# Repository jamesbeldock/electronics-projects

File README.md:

# Electronics Projects

Various electronics projects, mostly for home automation. I am not a professional electrical engineer. See Disclaimer :) 

## LED Control Board `XC-0001 Rev 2`

Originally designed to power 12V lighted house numerals from Luxello and constant-current LEDs using an off-board part.

## Disclaimer
This repository contains electronics designs, schematics, board layouts, firmware, and related materials (the "Materials") provided for educational and informational purposes only. The Materials are distributed under the MIT License (see LICENSE).

**No warranty.** The Materials are provided "AS IS", without warranty of any kind, express or implied, including but not limited to the warranties of merchantability, fitness for a particular purpose, correctness, and non-infringement. No representation is made that any design is safe, functional, complete, accurate, or suitable for any purpose.
Assumption of risk. Working with electronics involves inherent risks, including but not limited to electric shock, fire, burns, exposure to hazardous materials, damage to property, and bodily injury or death — particularly where mains voltage, lithium chemistries, high currents, RF emissions, or stored energy (capacitors, inductors) are involved. You assume all risk arising from any use, construction, modification, or operation of the Materials.

**No liability.** In no event shall the author(s) or copyright holder(s) be liable for any claim, damages, or other liability — whether in an action of contract, tort (including negligence), or otherwise — arising from, out of, or in connection with the Materials or their use, including any direct, indirect, incidental, special, exemplary, consequential, or punitive damages, regardless of the theory of liability and even if advised of the possibility of such damages.

**Your responsibility.** You are solely responsible for verifying every design before use; for ensuring compliance with all applicable codes, standards, and regulations (including but not limited to electrical, building, fire, and RF/EMC regulations such as those of the FCC, IEC, UL, and CE); for obtaining any required certifications or inspections; and for the safe construction, testing, and operation of anything derived from the Materials. Designs are not certified, have not necessarily been tested, and may contain errors, omissions, or latent defects.

**Not professional advice.** Nothing herein constitutes engineering, legal, or safety advice. Consult a qualified licensed professional before relying on any design.

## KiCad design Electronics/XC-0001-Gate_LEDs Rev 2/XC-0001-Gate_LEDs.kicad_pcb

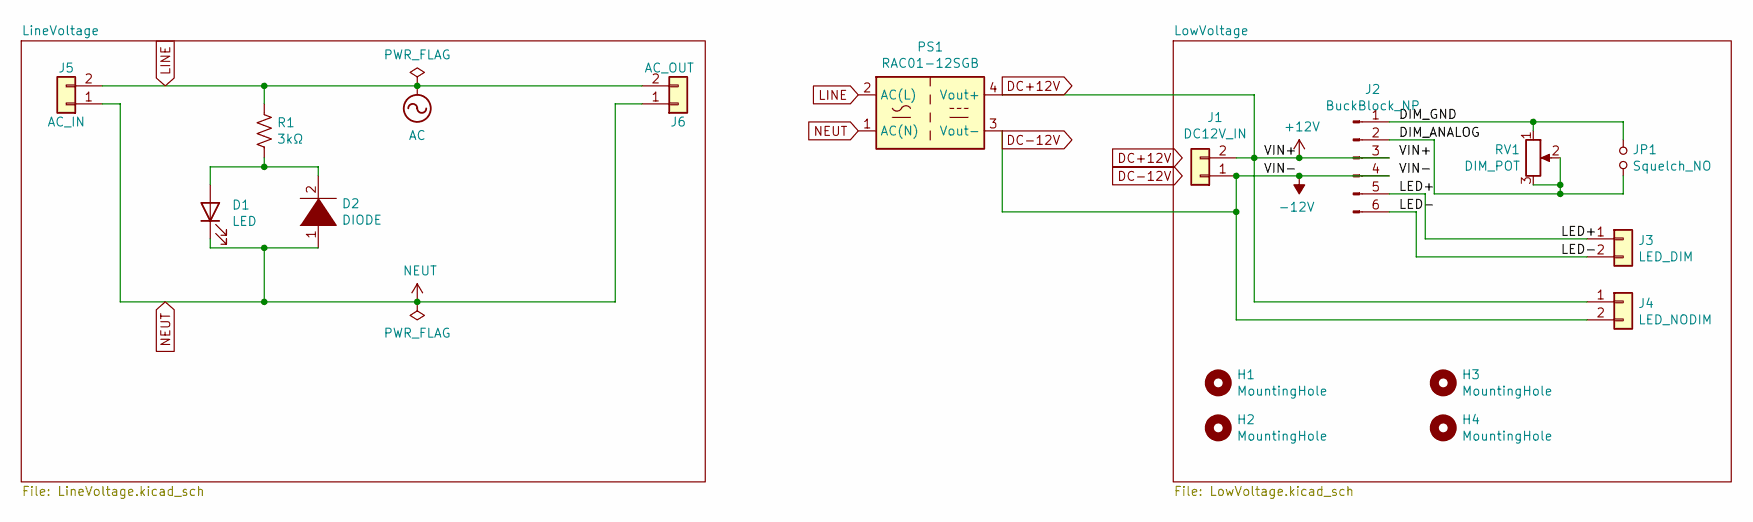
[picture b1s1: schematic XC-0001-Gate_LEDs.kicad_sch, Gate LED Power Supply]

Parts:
D1: LED; SolderWire-0.5sqmm_1x02_P4.8mm_D0.9mm_OD2.3mm
D2: DIODE; D_T-1_P10.16mm_Horizontal
H1, H2, H3, H4: MountingHole; MountingHole_3.2mm_M3_DIN965_Pad_TopOnly
J1: DC12V_IN; SolderWire-0.25sqmm_1x02_P4.2mm_D0.65mm_OD1.7mm
J2: BuckBlock_NP; SolderWire-1sqmm_1x06_P7.8mm_D1.4mm_OD3.9mm
J3: LED_DIM; SolderWire-0.25sqmm_1x02_P4.2mm_D0.65mm_OD1.7mm
J4: LED_NODIM; SolderWire-0.25sqmm_1x02_P4.2mm_D0.65mm_OD1.7mm
J5: AC_IN; SolderWire-0.75sqmm_1x02_P7mm_D1.25mm_OD3.5mm
J6: AC_OUT; SolderWire-0.75sqmm_1x02_P7mm_D1.25mm_OD3.5mm
JP1: Squelch_NO; SolderWire-0.25sqmm_1x02_P4.2mm_D0.65mm_OD1.7mm
PS1: RAC01-12SGB; Converter_ACDC_RECOM_RAC01-xxSGB_THT
R1: 3kΩ; R_1210_3225Metric_Pad1.30x2.65mm_HandSolder
RV1: DIM_POT; Potentiometer_Piher_PC-16_Single_Horizontal

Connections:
+12V: J1.2, J2.3, J4.1, PS1.4 (Vout+)
/DIM_ANALOG: J2.2, JP1.2, RV1.2, RV1.3
/DIM_GND: J2.1, JP1.1, RV1.1
/LED+: J2.5, J3.1
/LED-: J2.6, J3.2
DC-12V: J1.1, J2.4, J4.2, PS1.3 (Vout-)
LINE: J5.2, J6.2, PS1.2 (AC(L)), R1.1
NEUT: D1.1 (K), D2.1 (K), J5.1, J6.1, PS1.1 (AC(N))
unnamed: D1.2 (A), D2.2 (A), R1.2

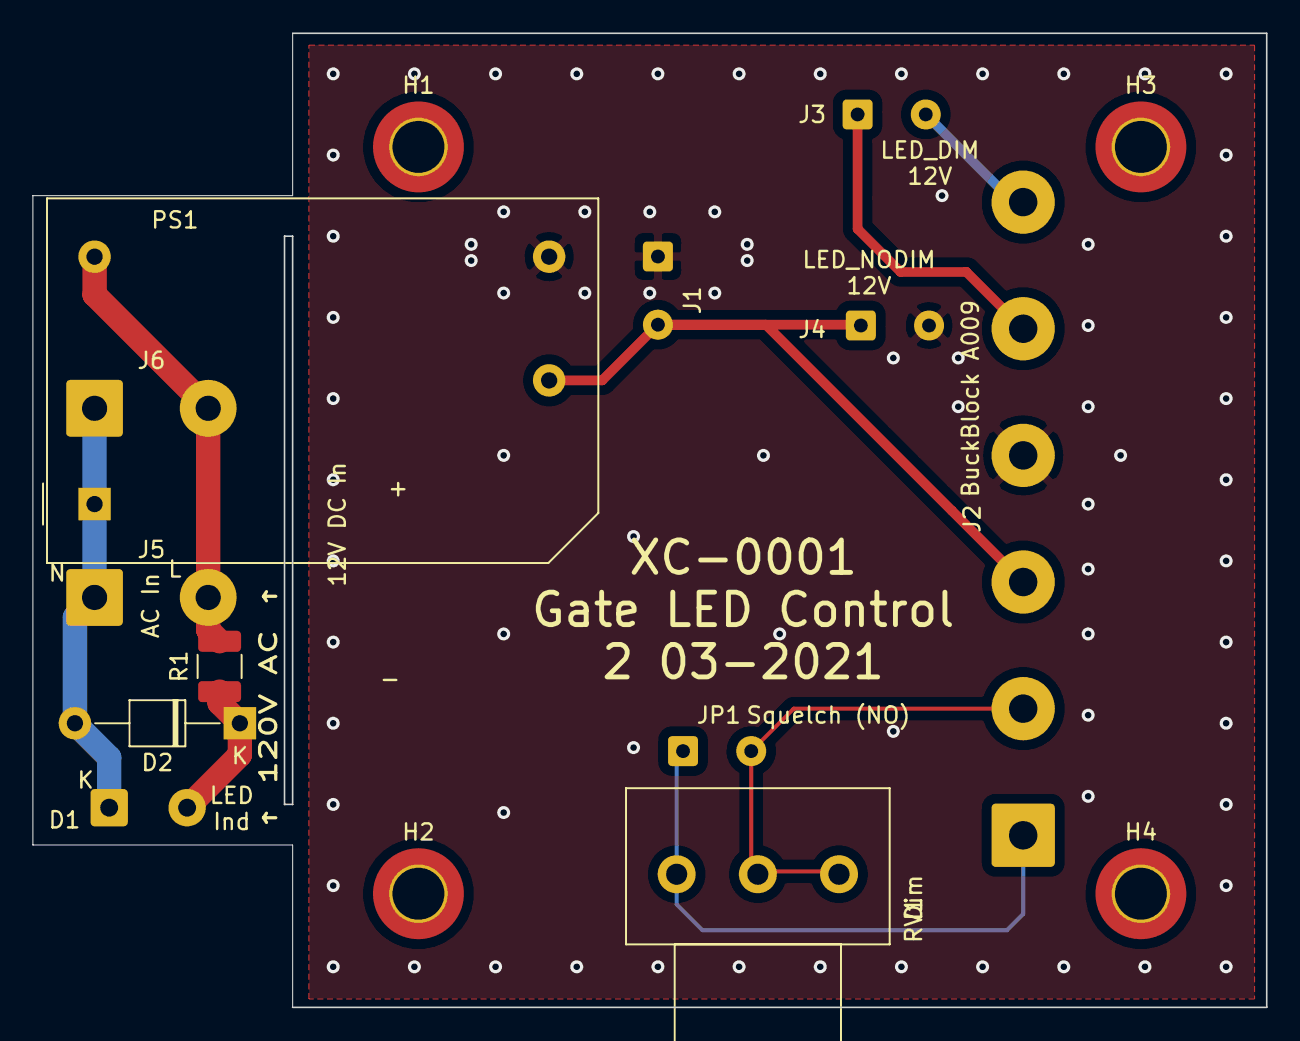
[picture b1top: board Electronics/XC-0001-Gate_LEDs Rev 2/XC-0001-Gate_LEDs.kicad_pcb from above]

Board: 2 copper layers, 76.0 x 60.0 mm, 16 parts (0 on the bottom side), 9 nets.

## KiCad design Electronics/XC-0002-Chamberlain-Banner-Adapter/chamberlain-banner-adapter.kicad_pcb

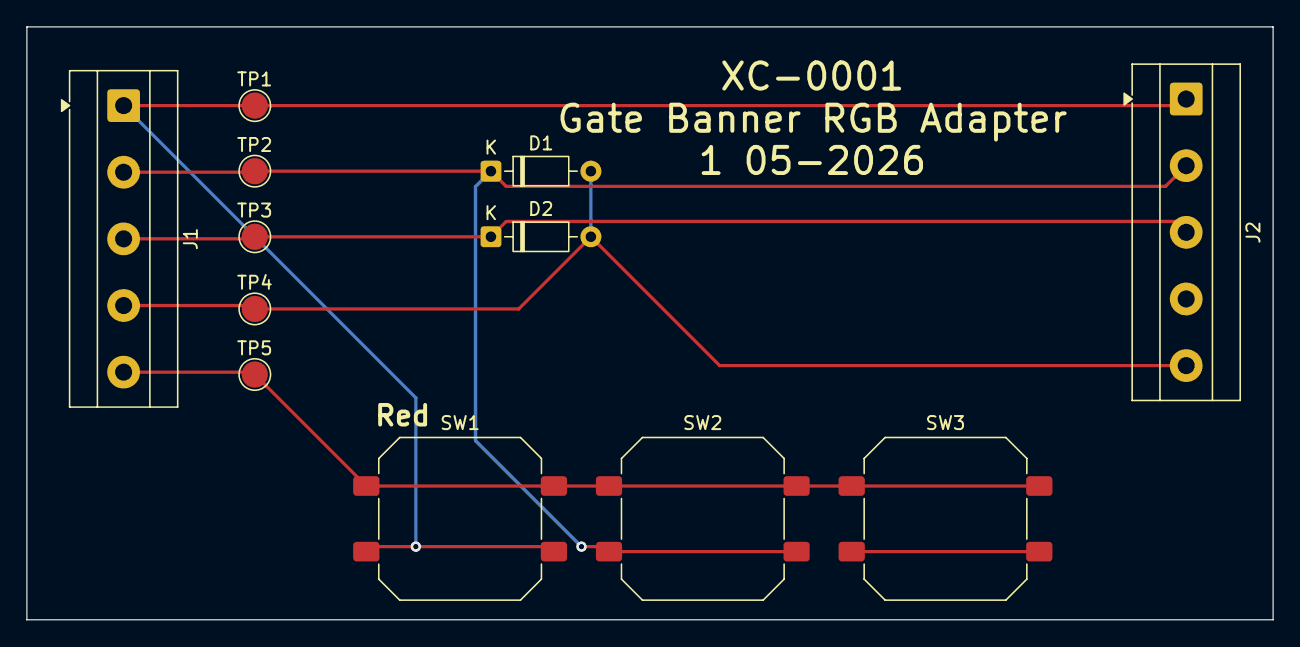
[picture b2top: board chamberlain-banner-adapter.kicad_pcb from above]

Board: 2 copper layers, 95.0 x 45.2 mm, 12 parts (0 on the bottom side), 5 nets.

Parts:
D1, D2: 1N914; D_DO-35_SOD27_P7.62mm_Horizontal
J1, J2: Conn_01x05_Socket; TerminalBlock_MetzConnect_Type101_RT01605HBWC_1x05_P5.08mm_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
SW1, SW2, SW3: SW_Push; SW_Push_1P1T_NO_CK_PTS125Sx43SMTR
TP1, TP2, TP3, TP4, TP5: TestPoint; TestPoint_Pad_D2.0mm

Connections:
/Blink: D1.2 (A), D2.2 (A), J1.4, J2.5, TP4.1 (1_1)
/Com –: J1.1, J2.1, SW1.2, TP1.1 (1_1)
/Green Output: D2.1 (K), J1.3, J2.3, TP3.1 (1_1)
/Red Output: D1.1 (K), J1.2, J2.2, SW2.2, TP2.1 (1_1)
unnamed: J1.5, SW1.1, SW2.1, SW3.1 (1_1), TP5.1 (1_1)

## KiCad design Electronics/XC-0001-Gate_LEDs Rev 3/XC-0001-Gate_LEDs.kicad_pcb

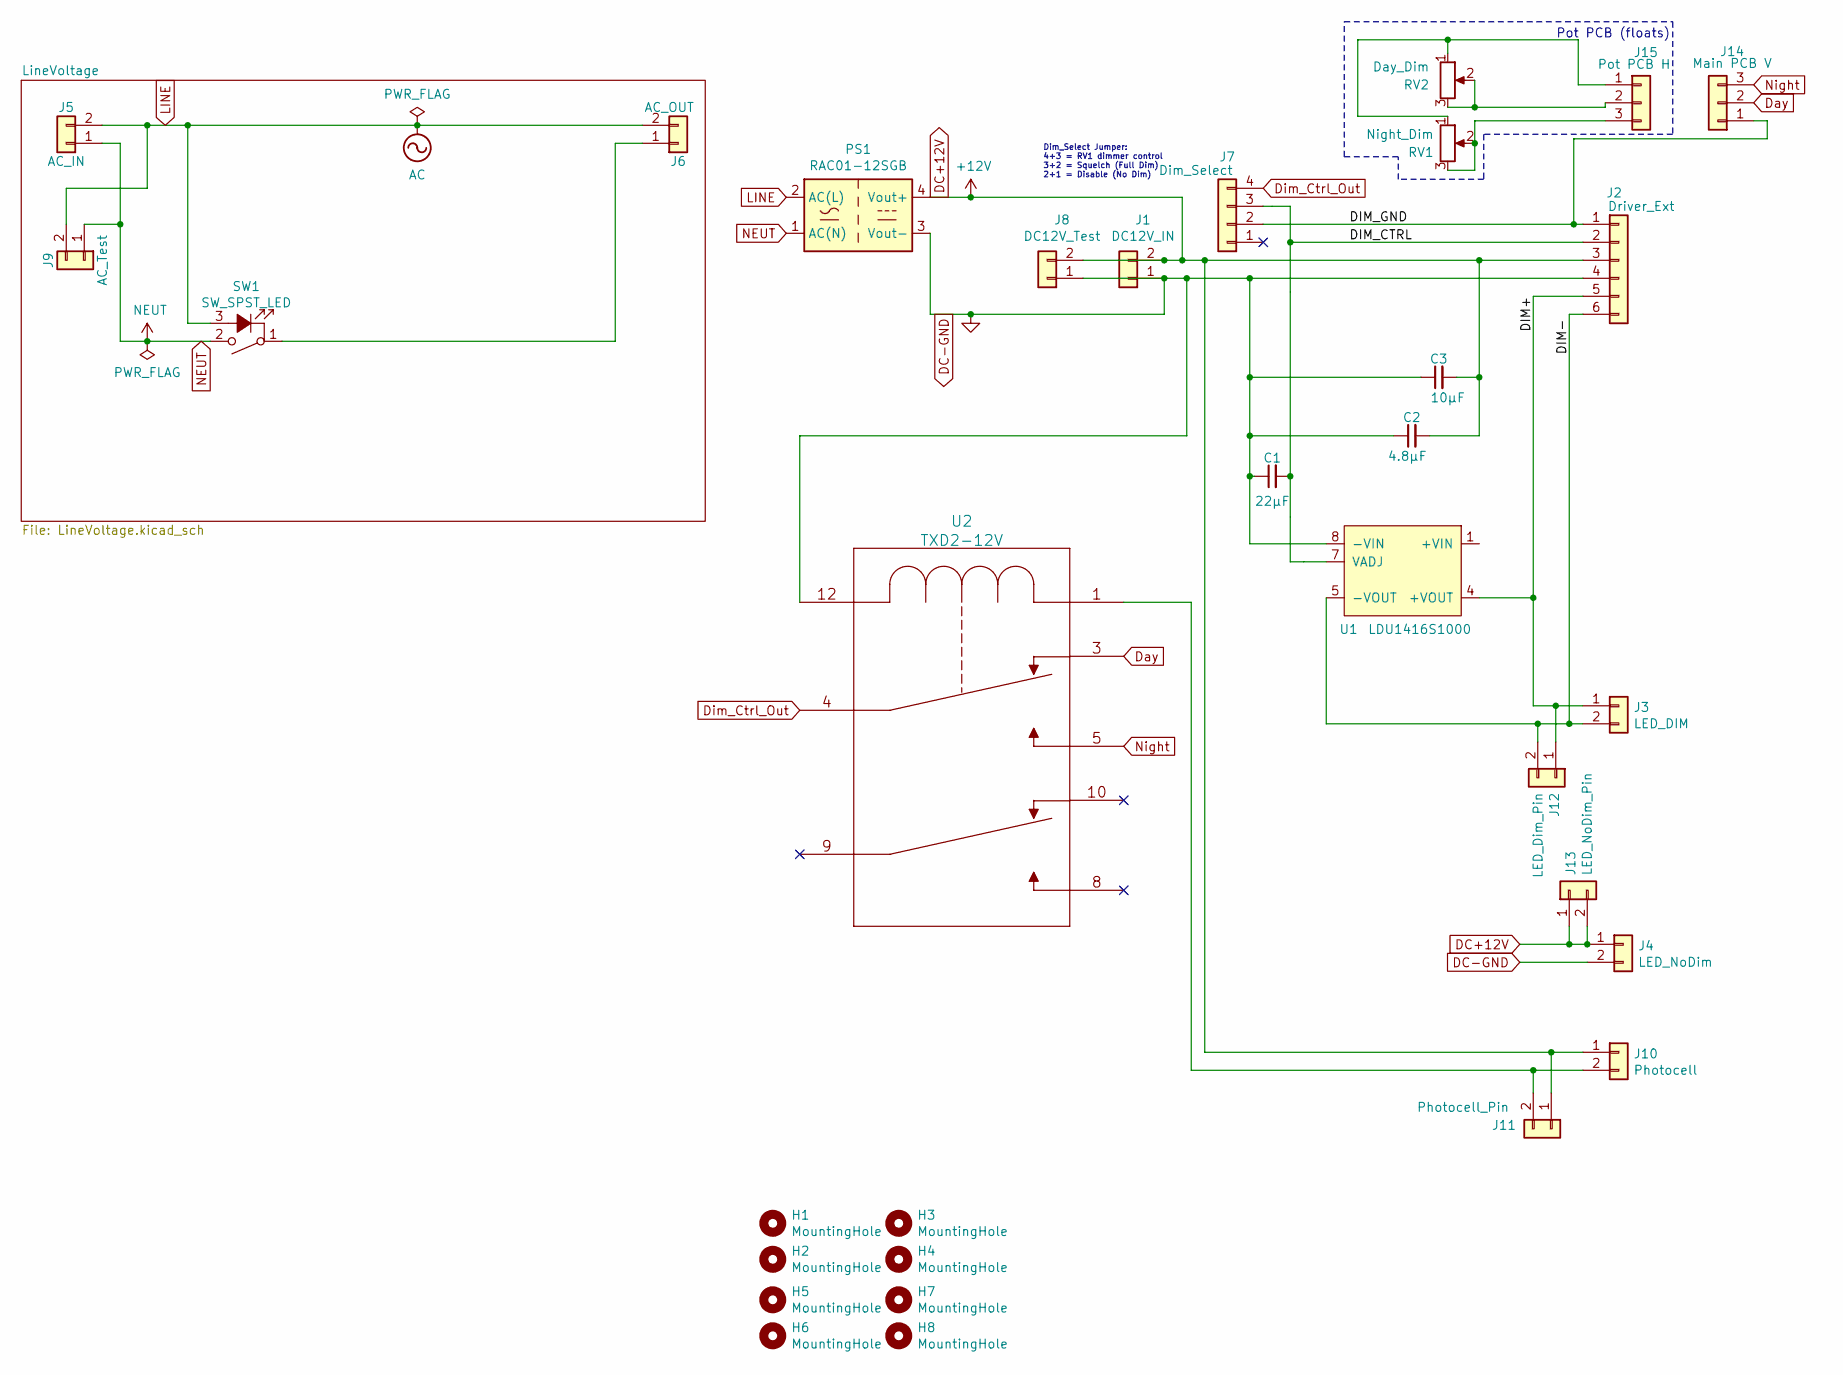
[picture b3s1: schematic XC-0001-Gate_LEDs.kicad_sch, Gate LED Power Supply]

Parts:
C1: 22µF; C_1206_3216Metric_Pad1.33x1.80mm_HandSolder; Digikey 1276-3107-1-ND
C2: 4.8µF; C_1206_3216Metric_Pad1.33x1.80mm_HandSolder; Digikey 1276-1133-1-ND
C3: 10µF; C_1206_3216Metric_Pad1.33x1.80mm_HandSolder; Digikey 1276-3147-1-ND
H1, H2, H3, H4, H5, H6, H7, H8: MountingHole; MountingHole_3.2mm_M3
J1: DC12V_IN; SolderWire-1.5sqmm_1x02_P7.8mm_D1.7mm_OD3.9mm
J2: Driver_Ext; SolderWire-1.5sqmm_1x06_Grouped2x3_P6mm_D1.7mm_OD3mm
J3: LED_DIM; PhoenixContact_MSTBA_2,5_2-G-5,08_1x02_P5.08mm_Horizontal
J4: LED_NoDim; PhoenixContact_MSTBA_2,5_2-G-5,08_1x02_P5.08mm_Horizontal
J5: AC_IN; 6160.0015 C8 Inlet (panel mount, PCB pins)
J6: AC_OUT; SolderWire-2sqmm_1x02_P7.8mm_D2mm_OD3.9mm_Relief
J7: Dim_Select; PinHeader_1x04_P2.54mm_Vertical; Digikey MTSW-104-07-G-S-170-ND
J8: DC12V_Test; Test Holes
J9: AC_Test; Test Holes
J10: Photocell; PhoenixContact_MSTBA_2,5_2-G-5,08_1x02_P5.08mm_Horizontal
J11: Photocell_Pin; PinHeader_1x02_P2.54mm_Vertical
J12: LED_Dim_Pin; PinHeader_1x02_P2.54mm_Vertical
J13: LED_NoDim_Pin; PinHeader_1x02_P2.54mm_Vertical
J14: Main PCB V; PinHeader_1x03_P2.54mm_Vertical
J15: Pot PCB H; PinHeader_1x03_P2.54mm_Vertical
PS1: RAC01-12SGB; Converter_ACDC_RECOM_RAC01-xxSGB_THT; Digikey ‎945-3046-ND‎
RV1: Night_Dim; Potentiometer_Piher_PC-16_Single_Horizontal; Digikey PDB181-K420K-203B-ND
RV2: Day_Dim; Potentiometer_Piher_PC-16_Single_Horizontal; Digikey PDB181-K420K-203B-ND
SW1: SW_SPST_LED; PhoenixContact_MSTBVA_2,5_3-G-5,08_1x03_P5.08mm_Vertical
U1: LDU1416S1000; Digikey ‎1470-2154-5-ND‎
U2: TXD2-12V; Digikey 255-2320-5-ND

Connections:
/DIM+: J2.5, J3.1, J12.1, U1.4 (+VOUT)
/DIM-: J2.6, J3.2, J12.2, U1.5 (-VOUT)
/DIM_CTRL: C1.2, J2.2, J7.3, U1.7 (VADJ)
/DIM_GND: J2.1, J7.2, J14.1
DC+12V: C2.2, C3.2, J1.2, J2.3, J4.1, J8.2, J10.1, J11.1, J13.1, J13.2, PS1.4 (Vout+); also elsewhere on the board
DC-GND: C1.1, C2.1, C3.1, J1.1, J2.4, J4.2, J8.1, PS1.3 (Vout-), U1.8 (-VIN), U2.12
Day: J14.2, U2.3
Dim_Ctrl_Out: J7.4, U2.4
LINE: J5.2, J6.2, J9.2, PS1.2 (AC(L)), SW1.3 (Line_In)
NEUT: J5.1, J9.1, PS1.1 (AC(N)), SW1.2 (Neutral_In)
unnamed: J6.1, SW1.1 (Neutral_Out)
unnamed: J10.2, J11.2, U2.1
unnamed: J15.1, RV1.1, RV2.1
unnamed: J15.3, RV1.2, RV1.3
unnamed: J15.2, RV2.2, RV2.3
Night: J14.3, U2.5

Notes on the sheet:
Dim_Select Jumper: 4+3 = RV1 dimmer control 3+2 = Squelch (Full Dim) 2+1 = Disable (No Dim)
Pot PCB (floats)

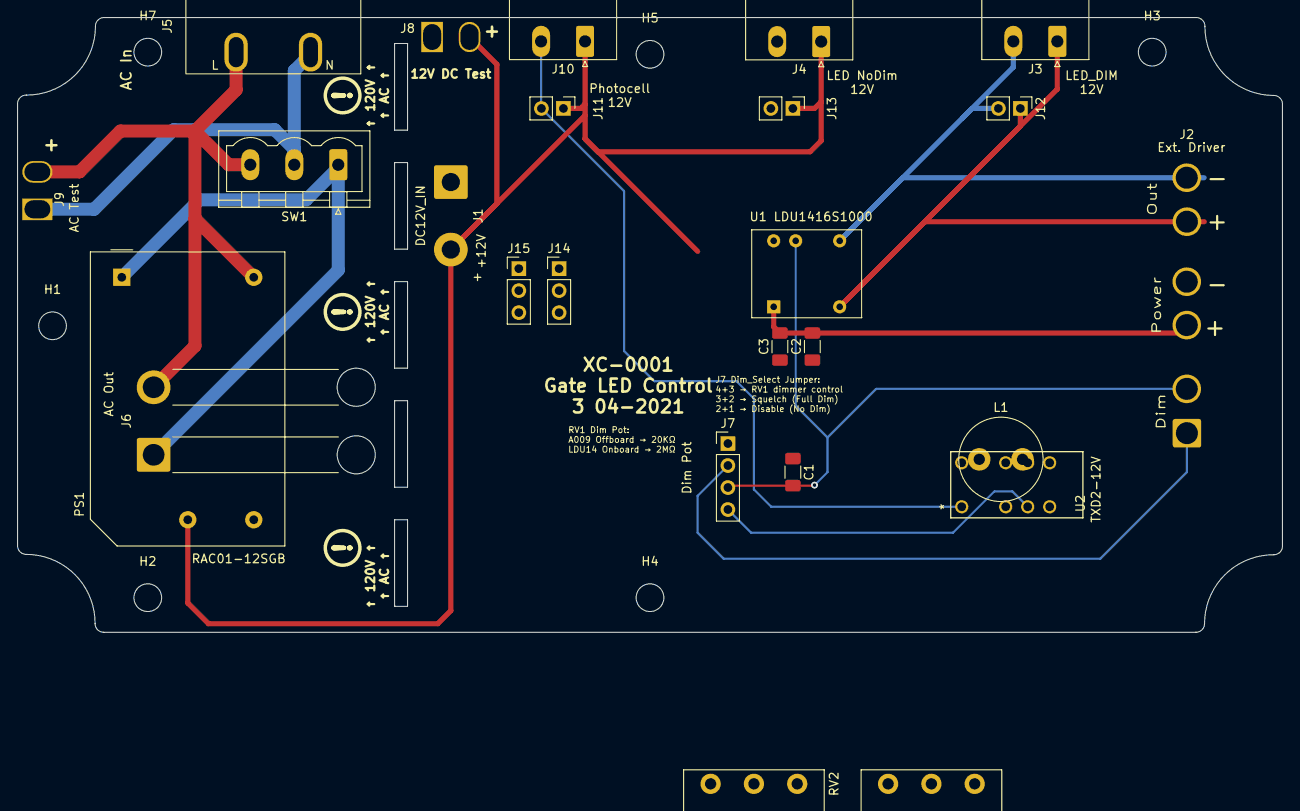
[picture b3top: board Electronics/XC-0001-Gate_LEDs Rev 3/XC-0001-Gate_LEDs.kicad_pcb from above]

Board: 2 copper layers, 146.1 x 71.0 mm, 33 parts (0 on the bottom side), 16 nets.

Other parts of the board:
L1: 68µH; L_Radial_D9.5mm_P5.00mm_Fastron_07HVP

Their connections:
DC+12V: L1.1; also elsewhere on the board

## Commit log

2021-02-08 Initial plan with BoM embedded
2021-02-14 Adding Electronics directory and reorganizing
2021-02-14 Add CAD files for LED base plate
2021-02-14 Move block diagram to Electronics dir
2021-02-14 rename KiCAD project
2021-02-14 Wasn't KiCAD project; starting fresh
2021-02-28 Rev 2 with AC/DC converter
2021-03-01 Reorganized directories
2021-03-01 Rename Rev 2
2021-03-02 Starting rev 3, still KiCad 5.x
2021-03-21 Version 2 updates
2021-03-21 Add XC custom footprints and symbols libraries
2021-03-21 Rev 3 major update, prior to Rev 2 upgrade notes
2021-04-03 Add notes on rev 2 > rev 3 changes
2021-04-03 Change power inlet to PCB mount C8 connector
2021-04-06 Add notes after Rev 2 gate install
2021-04-06 Rev 3a Custom Box, first attempt
2021-04-25 Add warning SVG
2021-04-25 Add new symbols to library
2021-04-25 Ignore backup
2021-04-25 Custom box revisions
2021-04-25 Adding new footprints
2021-04-26 Remove inductor to debug false pin connection
2023-06-30 Update to KiCAD 7.x, bump Rev. to 2a (not manufactured)
2023-06-30 Move highlevel.png to Rev 2 directory
2023-07-06 Bump KiCad version top 7 for Rev 3 (not manufactured)
2023-07-06 Ignore .DS_Store
2023-07-06 Add Olimex boards
2026-06-14 XC-0002 Chamberlain to Banner Indicator RGB
2026-06-14 Added MIT companion disclaimer.
2026-06-14 Add disclaimer about materials and user responsibility
    Added a disclaimer regarding the use and risks associated with the materials provided in the repository.
2026-06-14 XC-0001 updated to KiCad 10.0
2026-06-14 Adding MIT License
2026-06-14 Enhance README with project description and disclaimer
    Added a brief description of the repository and a disclaimer.
2026-06-14 Add LED Control Board section to README
    Added details about the LED Control Board including images.
2026-06-14 Remove height attributes from images in README
2026-06-14 Add hero images

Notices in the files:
parts and their libraries:
Copyright 2016 Accelerated Designs. All rights reserved.
